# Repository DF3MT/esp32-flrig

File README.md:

<h1 align="center">ESP32 CAT Remote Panel</h1>

<p align="center"><sub><strong><a href="https://en.wikipedia.org/wiki/Computer_Aided_Transceiver">CAT</a></strong> = <a href="https://en.wikipedia.org/wiki/Computer_Aided_Transceiver">Computer Aided Transceiver</a> (not Caterpillar)</sub></p>

<p align="center">
  <a href="#deutsch">🇩🇪 Deutsch</a> ·
  <a href="#english">🇬🇧 English</a>
</p>

<p align="center">
  <strong>DE:</strong> Funkfernbedienung mit Touch-Display, <a href="https://en.wikipedia.org/wiki/Computer_Aided_Transceiver">CAT</a>, <a href="https://de.wikipedia.org/wiki/WLAN">WiFi</a>-Audio, <a href="https://de.wikipedia.org/wiki/FT8_(Amateurfunk)">FT8</a> · bis zu <strong>3× Funk + <a href="https://de.wikipedia.org/wiki/Rotor_(Antenne)">Rotor</a></strong><br>
  <strong>EN:</strong> <a href="https://en.wikipedia.org/wiki/Amateur_radio">Ham radio</a> remote panel with touch UI, <a href="https://en.wikipedia.org/wiki/Computer_Aided_Transceiver">CAT</a>, <a href="https://en.wikipedia.org/wiki/Wi-Fi">WiFi</a> audio, <a href="https://en.wikipedia.org/wiki/FT8_(digital_mode)">FT8</a> · up to <strong>3× radios + <a href="https://en.wikipedia.org/wiki/Antenna_rotator">rotor</a></strong>
</p>

<p align="center">
  <a href="https://de.wikipedia.org/wiki/Icom">ICOM</a> <a href="https://de.wikipedia.org/wiki/CI-V">CI-V</a> · <a href="https://de.wikipedia.org/wiki/Yaesu">Yaesu</a> <a href="https://en.wikipedia.org/wiki/Computer_Aided_Transceiver">CAT</a> · <a href="https://www.xiegu.com/">Xiegu</a> · <a href="https://github.com/w1hkj/flrig">flrig</a> · <a href="https://physics.princeton.edu/pulsar/k1jt/wsjtx.html">WSJT-X</a> · <a href="https://en.wikipedia.org/wiki/Hamlib">Hamlib</a> <a href="https://hamlib.sourceforge.net/html/rigctld.1.html">rigctld</a> · <a href="https://hamlib.sourceforge.net/html/rotctld.1.html">rotctld</a>
</p>

<p align="center">
  <a href="#deutsch">📖 DE</a> ·
  <a href="#english">📖 EN</a> ·
  <a href="docs/GUIDE_DE.md">Leitfaden (DE)</a> ·
  <a href="hardware/esp32-flrig-shield/README.md">🛠️ PCB</a> ·
  <a href="docs/RADIOS.md">📻 Radios</a> ·
  <a href="docs/ISOLATION.md">🔌 Isolation</a> ·
  <a href="docs/MULTI_RADIO_DE.md">📡 3× DE</a> ·
  <a href="docs/MULTI_RADIO_EN.md">📡 3× EN</a> ·
  <a href="docs/GLOSSARY.md">📚 Glossar</a> ·
  <a href="flasher/index.html">⚡ Flasher</a>
</p>

---

## Deutsch

### Was ist das?

Ein **[ESP32](https://de.wikipedia.org/wiki/ESP32)-Panel** (z. B. [Cheap Yellow Display](https://github.com/witnessmenow/ESP32-Cheap-Yellow-Display)) oder **[ESP32-S3](https://www.espressif.com/en/products/socs/esp32-s3) + Interface-Shield** steuert bis zu **drei [Funkgeräten](https://de.wikipedia.org/wiki/Transceiver) gleichzeitig** über **[WiFi](https://de.wikipedia.org/wiki/WLAN)**:

| Kanal | Anbindung | [CAT](https://en.wikipedia.org/wiki/Computer_Aided_Transceiver) → PC | Audio → PC (eigenes [UDP](https://de.wikipedia.org/wiki/User_Datagram_Protocol)-Paar) |
|-------|-----------|----------|------------------------------|
| **A** | [RJ45](https://de.wikipedia.org/wiki/RJ-45) / [I2S](https://de.wikipedia.org/wiki/I%C2%B2S) | `:4532` | `4533` / `4534` |
| **B** | [USB-A](https://de.wikipedia.org/wiki/USB) J5 | `:4536` | `4538` / `4539` |
| **C** | [USB](https://de.wikipedia.org/wiki/Universal_Serial_Bus)-A J6 | `:4540` | `4541` / `4542` |
| **[Rotor](https://de.wikipedia.org/wiki/Rotor_(Antenne))** | [GPIO](https://de.wikipedia.org/wiki/General_Purpose_Input/Output) | `:4535` | — |

Ideal für **[FT8](https://de.wikipedia.org/wiki/FT8_(Amateurfunk))/[WSJT-X](https://physics.princeton.edu/pulsar/k1jt/wsjtx.html)** am PC ohne [USB-Kabel](https://de.wikipedia.org/wiki/Universal_Serial_Bus) zum Funk. Shield **Rev C** trennt die **Masse jedes Funkgeräts [galvanisch](https://de.wikipedia.org/wiki/Galvanische_Trennung)** ([Isolation](docs/ISOLATION.md)).

**3 [Funkgeräte](https://de.wikipedia.org/wiki/Transceiver)** = am PC **3 parallele, unabhängige** Ketten (je ein [rigctld](https://hamlib.sourceforge.net/html/rigctld.1.html)-[TCP](https://de.wikipedia.org/wiki/Transmission_Control_Protocol)-Port + ein Audio-[UDP](https://de.wikipedia.org/wiki/User_Datagram_Protocol)-Paar + eigenes PC-Audiogerät, z. B. [VB-Cable](https://vb-audio.com/Cable/) A/B/C). Der ESP mischt die Streams **nicht**.

**[CAT](https://en.wikipedia.org/wiki/Computer_Aided_Transceiver)** = **[Computer Aided Transceiver](https://en.wikipedia.org/wiki/Computer_Aided_Transceiver)** (Steuerprotokoll, z. B. [CI-V](https://de.wikipedia.org/wiki/CI-V) / [Yaesu CAT](https://en.wikipedia.org/wiki/Computer_Aided_Transceiver)).

| PC-Instanz | [rigctld](https://hamlib.sourceforge.net/html/rigctld.1.html) ([CAT](https://en.wikipedia.org/wiki/Computer_Aided_Transceiver)) | Audio RX / TX ([UDP](https://de.wikipedia.org/wiki/User_Datagram_Protocol)) | Web |
|------------|---------------|---------------------|-----|
| Funk A | **4532** | **4533** / **4534** | `/audio` |
| Funk B | **4536** | **4538** / **4539** | `/audio_b` |
| Funk C | **4540** | **4541** / **4542** | `/audio_c` |
| [Rotor](https://de.wikipedia.org/wiki/Rotor_(Antenne)) | **4535** ([rotctld](https://hamlib.sourceforge.net/html/rotctld.1.html)) | — | — |

Details: [MULTI_RADIO_DE.md](docs/MULTI_RADIO_DE.md) · Beispiel-Konfig: [ft8_config.example-3radio.json](scripts/ft8_config.example-3radio.json)

### Unterstützte [Funkgeräte](https://de.wikipedia.org/wiki/Transceiver)

| Hersteller | Modelle |
|------------|---------|
| **[Xiegu](https://www.xiegu.com/)** | G90, [X6100](https://www.xiegu.com/), [X6200](https://www.xiegu.com/) |
| **[Yaesu](https://de.wikipedia.org/wiki/Yaesu)** | FT-991A, FT-910, FT-DX10, FT-DX101D/MP, FT-891, FT-897, FT-857 |
| Referenz | [ICOM](https://de.wikipedia.org/wiki/Icom) IC-7300 |

Profil in der Web-UI → Baudrate & Protokoll automatisch: [RADIOS.md](docs/RADIOS.md)

### Schnellstart

**Firmware (1× Funk, [CYD](https://github.com/witnessmenow/ESP32-Cheap-Yellow-Display)):**

```bash
pio run -e esp32-cyd -t upload
pio run -e esp32-cyd -t uploadfs
```

**Firmware (3× Funk + [Rotor](https://de.wikipedia.org/wiki/Rotor_(Antenne)), Shield Rev C + [ESP32-S3](https://www.espressif.com/en/products/socs/esp32-s3)):**

```bash
pio run -e esp32-flrig-shield -t upload
pio run -e esp32-flrig-shield -t uploadfs
```

Oder **[Web-Flasher](flasher/index.html)** im Browser.

| Modus | [SSID](https://de.wikipedia.org/wiki/Service_Set_Identifier) / IP | Konfiguration |
|-------|-----------|---------------|
| AP (Werk) | `ESP32-CAT-Panel` / `192.168.4.1` | http://192.168.4.1/ |
| [WLAN](https://de.wikipedia.org/wiki/WLAN) | [DHCP](https://de.wikipedia.org/wiki/Dynamic_Host_Configuration_Protocol) | Funkprofil wählen |

**[CAT](https://en.wikipedia.org/wiki/Computer_Aided_Transceiver) testen ([Computer Aided Transceiver](https://en.wikipedia.org/wiki/Computer_Aided_Transceiver)):**

```bash
rigctl -m 2 -r 192.168.4.1:4532 f    # Funk A
rigctl -m 2 -r 192.168.4.1:4536 f    # Funk B
rigctl -m 2 -r 192.168.4.1:4540 f    # Funk C
rotctl -m 2 -r 192.168.4.1:4535 p    # Rotor
```

### [Rotor](https://de.wikipedia.org/wiki/Rotor_(Antenne)) ([Hamlib](https://en.wikipedia.org/wiki/Hamlib) [rotctld](https://hamlib.sourceforge.net/html/rotctld.1.html))

Zwei **Taster** (Azimut) und zwei **[Open-Collector](https://de.wikipedia.org/wiki/Offener_Kollektor)-Ausgänge** für Relais ([NPN](https://de.wikipedia.org/wiki/Bipolartransistor) + [Freilaufdiode](https://de.wikipedia.org/wiki/Freilaufdiode) extern).

| Richtung (`M`) | Wert | OC-[GPIO](https://de.wikipedia.org/wiki/General_Purpose_Input/Output) ([CYD](https://github.com/witnessmenow/ESP32-Cheap-Yellow-Display)) |
|----------------|------|---------------|
| Links (CCW) | 8 | **18** |
| Rechts (CW) | 16 | **19** |
| Taster CCW / CW | — | **27** / **5** |

`OUTPUT_OPEN_DRAIN`: **LOW** = Relais ein. Port **4535** (nicht 4533 — Audio-[UDP](https://de.wikipedia.org/wiki/User_Datagram_Protocol)).

### Interface-Shield (Dokumentation)

| Dokument | Inhalt |
|----------|--------|
| [Shield README](hardware/esp32-flrig-shield/README.md#deutsch) | Übersicht (DE/EN) |
| [Schaltplan](hardware/esp32-flrig-shield/docs/SCHEMATIC.md) | Logik, Isolation |
| [Kabel](hardware/esp32-flrig-shield/docs/CABLE_ASSEMBLY.md) | RJ45 / Funk |
| [RJ45-Pinout](hardware/esp32-flrig-shield/docs/RJ45_PINOUT.md) | Steckerbelegung |

### [FT8](https://de.wikipedia.org/wiki/FT8_(Amateurfunk)) / [WSJT-X](https://physics.princeton.edu/pulsar/k1jt/wsjtx.html)

```bash
pip install -r scripts/requirements-ft8.txt
cp scripts/ft8_config.example.json ~/.config/esp32-flrig/ft8.json
python3 scripts/ft8_setup.py --config ~/.config/esp32-flrig/ft8.json --test-cat --start
```

| OS | Skript |
|----|--------|
| [Linux](https://de.wikipedia.org/wiki/Linux) | `./scripts/ft8_setup.sh 192.168.4.1 --pa --start` |
| [Windows](https://de.wikipedia.org/wiki/Microsoft_Windows) | `.\scripts\ft8_windows_setup.ps1 -EspHost 192.168.4.1 -InstallVbCable -StartBridge` |

### Hardware ([CYD](https://github.com/witnessmenow/ESP32-Cheap-Yellow-Display), Kanal A)

| Signal | [GPIO](https://de.wikipedia.org/wiki/General_Purpose_Input/Output) |
|--------|------|
| [CAT](https://en.wikipedia.org/wiki/Computer_Aided_Transceiver) RX / TX | 16 / 17 |
| [I2S](https://de.wikipedia.org/wiki/I%C2%B2S) BCLK / LRCK | 26 / 25 |
| [I2S](https://de.wikipedia.org/wiki/I%C2%B2S) DOUT / DIN | 22 / 4 |
| [Potis](https://de.wikipedia.org/wiki/Potentiometer) 1–5 | 32, 35, 34, 39, 36 |
| [Rotor](https://de.wikipedia.org/wiki/Rotor_(Antenne)) Taster / OC | 27, 5 / 18, 19 |

### Weitere Dokumentation

| Thema | Link |
|-------|------|
| Ausführlicher Leitfaden | [GUIDE_DE.md](docs/GUIDE_DE.md) (Deutsch) |
| [Hamlib](https://en.wikipedia.org/wiki/Hamlib) [rigctld](https://hamlib.sourceforge.net/html/rigctld.1.html) / [rotctld](https://hamlib.sourceforge.net/html/rotctld.1.html) | [rigctld](https://hamlib.sourceforge.net/html/rigctld.1.html) · [rotctld](https://hamlib.sourceforge.net/html/rotctld.1.html) |
| Audio-Monitor | http://\<ESP-IP\>/audio |

---

## English

### What is this?

An **[ESP32](https://en.wikipedia.org/wiki/ESP32) panel** (e.g. [Cheap Yellow Display](https://github.com/witnessmenow/ESP32-Cheap-Yellow-Display)) or **[ESP32-S3](https://www.espressif.com/en/products/socs/esp32-s3) + interface shield** controls up to **three [transceivers](https://en.wikipedia.org/wiki/Transceiver) at once** over **[WiFi](https://en.wikipedia.org/wiki/Wi-Fi)**:

| Channel | Connection | [CAT](https://en.wikipedia.org/wiki/Computer_Aided_Transceiver) → PC | Audio → PC (own [UDP](https://en.wikipedia.org/wiki/User_Datagram_Protocol) pair) |
|---------|------------|----------|---------------------------|
| **A** | [RJ45](https://en.wikipedia.org/wiki/Registered_jack) / [I2S](https://en.wikipedia.org/wiki/I%C2%B2S) | `:4532` | `4533` / `4534` |
| **B** | [USB-A](https://en.wikipedia.org/wiki/USB) J5 | `:4536` | `4538` / `4539` |
| **C** | [USB](https://en.wikipedia.org/wiki/USB)-A J6 | `:4540` | `4541` / `4542` |
| **[Rotor](https://en.wikipedia.org/wiki/Antenna_rotator)** | [GPIO](https://en.wikipedia.org/wiki/General-purpose_input/output) | `:4535` | — |

Built for **[FT8](https://en.wikipedia.org/wiki/FT8_(digital_mode))/[WSJT-X](https://physics.princeton.edu/pulsar/k1jt/wsjtx.html)** on a PC without [USB cables](https://en.wikipedia.org/wiki/USB) to each radio. Shield **Rev C** uses **[galvanic isolation](https://en.wikipedia.org/wiki/Galvanic_isolation)** per radio ([ISOLATION.md](docs/ISOLATION.md)).

**3 radios** = on the PC **3 parallel, independent** chains (one [rigctld](https://hamlib.sourceforge.net/html/rigctld.1.html) [TCP](https://en.wikipedia.org/wiki/Transmission_Control_Protocol) port + one audio [UDP](https://en.wikipedia.org/wiki/User_Datagram_Protocol) pair + separate PC audio device each, e.g. [VB-Cable](https://vb-audio.com/Cable/) A/B/C). The ESP does **not** mix streams.

**[CAT](https://en.wikipedia.org/wiki/Computer_Aided_Transceiver)** = **[Computer Aided Transceiver](https://en.wikipedia.org/wiki/Computer_Aided_Transceiver)** (control protocol) — not construction equipment.

| PC instance | [rigctld](https://hamlib.sourceforge.net/html/rigctld.1.html) ([CAT](https://en.wikipedia.org/wiki/Computer_Aided_Transceiver)) | Audio RX / TX ([UDP](https://en.wikipedia.org/wiki/User_Datagram_Protocol)) | Web |
|-------------|---------------|---------------------|-----|
| Radio A | **4532** | **4533** / **4534** | `/audio` |
| Radio B | **4536** | **4538** / **4539** | `/audio_b` |
| Radio C | **4540** | **4541** / **4542** | `/audio_c` |
| [Rotor](https://en.wikipedia.org/wiki/Antenna_rotator) | **4535** ([rotctld](https://hamlib.sourceforge.net/html/rotctld.1.html)) | — | — |

Details: [MULTI_RADIO_EN.md](docs/MULTI_RADIO_EN.md) · Example config: [ft8_config.example-3radio.json](scripts/ft8_config.example-3radio.json)

### Supported radios

| Vendor | Models |
|--------|--------|
| **[Xiegu](https://www.xiegu.com/)** | G90, X6100, X6200 |
| **[Yaesu](https://en.wikipedia.org/wiki/Yaesu_(brand))** | FT-991A, FT-910, FT-DX10, FT-DX101D/MP, FT-891, FT-897, FT-857 |
| Reference | [ICOM](https://en.wikipedia.org/wiki/Icom) IC-7300 |

Select a profile in the web UI: [RADIOS.md](docs/RADIOS.md)

### Quick start

**Firmware (single radio, [CYD](https://github.com/witnessmenow/ESP32-Cheap-Yellow-Display)):**

```bash
pio run -e esp32-cyd -t upload
pio run -e esp32-cyd -t uploadfs
```

**Firmware (3 radios + [rotor](https://en.wikipedia.org/wiki/Antenna_rotator), Shield Rev C + [ESP32-S3](https://www.espressif.com/en/products/socs/esp32-s3)):**

```bash
pio run -e esp32-flrig-shield -t upload
pio run -e esp32-flrig-shield -t uploadfs
```

Or the **[Web Flasher](flasher/index.html)** in your browser.

| Mode | [SSID](https://en.wikipedia.org/wiki/Service_set_(802.11_network)) / IP | Config |
|------|-----------|--------|
| AP (default) | `ESP32-CAT-Panel` / `192.168.4.1` | http://192.168.4.1/ |
| [WiFi](https://en.wikipedia.org/wiki/Wi-Fi) STA | [DHCP](https://en.wikipedia.org/wiki/Dynamic_Host_Configuration_Protocol) | Select radio profile |

**Test [CAT](https://en.wikipedia.org/wiki/Computer_Aided_Transceiver) ([Computer Aided Transceiver](https://en.wikipedia.org/wiki/Computer_Aided_Transceiver)):**

```bash
rigctl -m 2 -r 192.168.4.1:4532 f    # Radio A
rigctl -m 2 -r 192.168.4.1:4536 f    # Radio B
rigctl -m 2 -r 192.168.4.1:4540 f    # Radio C
rotctl -m 2 -r 192.168.4.1:4535 p    # Rotor
```

### [Rotor](https://en.wikipedia.org/wiki/Antenna_rotator) ([Hamlib](https://en.wikipedia.org/wiki/Hamlib) [rotctld](https://hamlib.sourceforge.net/html/rotctld.1.html))

Two **buttons** (azimuth) and two **[open-collector](https://en.wikipedia.org/wiki/Open_collector)** outputs for relays (external [NPN](https://en.wikipedia.org/wiki/Bipolar_junction_transistor) + [flyback diode](https://en.wikipedia.org/wiki/Flyback_diode)).

| Direction (`M`) | Value | OC [GPIO](https://en.wikipedia.org/wiki/General-purpose_input/output) ([CYD](https://github.com/witnessmenow/ESP32-Cheap-Yellow-Display)) |
|-----------------|-------|---------------|
| Left (CCW) | 8 | **18** |
| Right (CW) | 16 | **19** |
| Buttons CCW / CW | — | **27** / **5** |

`OUTPUT_OPEN_DRAIN`: **LOW** = relay on. Port **4535** (not 4533 — audio [UDP](https://en.wikipedia.org/wiki/User_Datagram_Protocol)).

### Interface shield (documentation)

| Document | Content |
|----------|---------|
| [Shield README](hardware/esp32-flrig-shield/README.md#english) | Overview (DE/EN) |
| [Schematic](hardware/esp32-flrig-shield/docs/SCHEMATIC.md) | Logic, isolation |
| [Cables](hardware/esp32-flrig-shield/docs/CABLE_ASSEMBLY.md) | RJ45 / radio |
| [RJ45 pinout](hardware/esp32-flrig-shield/docs/RJ45_PINOUT.md) | Connector pins |

### [FT8](https://en.wikipedia.org/wiki/FT8_(digital_mode)) / [WSJT-X](https://physics.princeton.edu/pulsar/k1jt/wsjtx.html)

```bash
pip install -r scripts/requirements-ft8.txt
cp scripts/ft8_config.example.json ~/.config/esp32-flrig/ft8.json
python3 scripts/ft8_setup.py --config ~/.config/esp32-flrig/ft8.json --test-cat --start
```

| OS | Script |
|----|--------|
| [Linux](https://en.wikipedia.org/wiki/Linux) | `./scripts/ft8_setup.sh 192.168.4.1 --pa --start` |
| [Windows](https://en.wikipedia.org/wiki/Microsoft_Windows) | `.\scripts\ft8_windows_setup.ps1 -EspHost 192.168.4.1 -InstallVbCable -StartBridge` |

### Hardware ([CYD](https://github.com/witnessmenow/ESP32-Cheap-Yellow-Display), channel A)

| Signal | [GPIO](https://en.wikipedia.org/wiki/General-purpose_input/output) |
|--------|------|
| [CAT](https://en.wikipedia.org/wiki/Computer_Aided_Transceiver) RX / TX | 16 / 17 |
| [I2S](https://en.wikipedia.org/wiki/I%C2%B2S) BCLK / LRCK | 26 / 25 |
| [I2S](https://en.wikipedia.org/wiki/I%C2%B2S) DOUT / DIN | 22 / 4 |
| Pots 1–5 | 32, 35, 34, 39, 36 |
| [Rotor](https://en.wikipedia.org/wiki/Antenna_rotator) buttons / OC | 27, 5 / 18, 19 |

[CAT](https://en.wikipedia.org/wiki/Computer_Aided_Transceiver) on [CYD](https://github.com/witnessmenow/ESP32-Cheap-Yellow-Display): **3.3 V [TTL](https://en.wikipedia.org/wiki/Transistor%E2%80%93transistor_logic)**; on the shield **[ISO7741](https://www.ti.com/product/ISO7741)** isolates [RJ45](https://en.wikipedia.org/wiki/Registered_jack) [CAT](https://en.wikipedia.org/wiki/Computer_Aided_Transceiver) from ESP ground.

### Project layout

```
esp32-flrig/
├── docs/              Guides, radio list, isolation
├── hardware/esp32-flrig-shield/
│   ├── docs/          Schematic, cables, RJ45
│   └── assets/        Block diagram
├── scripts/           FT8 setup (Linux / Windows)
├── src/               Firmware
└── flasher/           Browser flasher
```

### Architecture

```
┌─────────────┐  rigctld :4532/4536/4540   ┌──────────────┐  isolated   ┌─────────┐
│ WSJT-X/flrig│◄──────────────────────────►│ ESP32 Panel  │◄───────────►│ 3× Radio│
└─────────────┘                            │ rotctld :4535│             └─────────┘
┌─────────────┐  rotctl                    │ WiFi audio   │
│ rotctl      │◄──────────────────────────►│ Touch + Web  │
└─────────────┘                            └──────────────┘
```

### More links

| Topic | Link |
|-------|------|
| Full guide | [GUIDE_DE.md](docs/GUIDE_DE.md) (German) |
| [Hamlib](https://en.wikipedia.org/wiki/Hamlib) [rigctld](https://hamlib.sourceforge.net/html/rigctld.1.html) / [rotctld](https://hamlib.sourceforge.net/html/rotctld.1.html) | [rigctld](https://hamlib.sourceforge.net/html/rigctld.1.html) · [rotctld](https://hamlib.sourceforge.net/html/rotctld.1.html) |
| Audio monitor | http://\<ESP-IP\>/audio |

---

<p align="center">
  <sub>License: see repository · Contributions welcome · <a href="#deutsch">🇩🇪</a> · <a href="#english">🇬🇧</a></sub>
</p>

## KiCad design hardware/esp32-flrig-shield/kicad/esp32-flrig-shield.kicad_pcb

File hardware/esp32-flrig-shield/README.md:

# ESP32-FLRIG Interface Shield

<p align="center">
  <a href="#deutsch">🇩🇪 Deutsch</a> ·
  <a href="#english">🇬🇧 English</a>
</p>

<p align="center">
  <sub><strong><a href="https://en.wikipedia.org/wiki/Computer_Aided_Transceiver">CAT</a></strong> = <a href="https://en.wikipedia.org/wiki/Computer_Aided_Transceiver">Computer Aided Transceiver</a></sub>
</p>

---

## Deutsch

### Übersicht

Dokumentation für ein **Interface-Shield** zwischen **[ESP32-S3](https://www.espressif.com/en/products/socs/esp32-s3)** ([USB-Host](https://de.wikipedia.org/wiki/USB)) bzw. optional **[CYD](https://github.com/witnessmenow/ESP32-Cheap-Yellow-Display)** (nur Funk **Kanal A**) und bis zu **drei Funkgeräten**:

| Anschluss | Funktion |
|-----------|----------|
| **J1 [RJ45](https://de.wikipedia.org/wiki/RJ-45)** | Funk **A**: +5 V, **[CAT](https://en.wikipedia.org/wiki/Computer_Aided_Transceiver)** ([UART](https://de.wikipedia.org/wiki/Asynchrone_Serielle_Schnittstelle)), **Line-Audio** |
| **J5 / J6** | **[USB-A](https://de.wikipedia.org/wiki/USB) Buchse** — Funk **B** und **C** ([CAT](https://en.wikipedia.org/wiki/Computer_Aided_Transceiver) + Audio per [USB](https://de.wikipedia.org/wiki/Universal_Serial_Bus)) |
| **U5 [USB2422](https://www.microchip.com/en-us/product/USB2422)** | 2-Port-Hub, Upstream **J3** → [ESP32-S3](https://www.espressif.com/en/products/socs/esp32-s3) OTG |
| **J7 / J3** | **[Rotor](https://de.wikipedia.org/wiki/Rotor_(Antenne))** (2× Taster, 2× [Open-Collector](https://de.wikipedia.org/wiki/Offener_Kollektor)) |
| **J2** | 2×10 für **[CYD](https://github.com/witnessmenow/ESP32-Cheap-Yellow-Display)** (Kanal A + [I2S](https://de.wikipedia.org/wiki/I%C2%B2S)) |

- **U1 [ISO7741](https://www.ti.com/product/ISO7741)** — [CAT](https://en.wikipedia.org/wiki/Computer_Aided_Transceiver) [galvanisch getrennt](https://de.wikipedia.org/wiki/Galvanische_Trennung) ([RJ45](https://de.wikipedia.org/wiki/RJ-45))  
- **U6/U7 [ADuM4160](https://www.analog.com/en/products/adum4160.html)** — [USB](https://de.wikipedia.org/wiki/Universal_Serial_Bus) [galvanisch](https://de.wikipedia.org/wiki/Galvanische_Trennung) getrennt (Funk B/C)  
- **T1/T2** — [Audio-Trafos](https://de.wikipedia.org/wiki/Transformator) (Funk A)  
- **[PCM5102](https://www.ti.com/product/PCM5102) + [INMP441](https://www.invensense.com/products/digital/inmp441/)** — [I2S](https://de.wikipedia.org/wiki/I%C2%B2S) (48 [kHz](https://de.wikipedia.org/wiki/Hertz))  

**3× Funk + 1× [Rotor](https://de.wikipedia.org/wiki/Rotor_(Antenne))** über **[WiFi](https://de.wikipedia.org/wiki/WLAN)**. **Keine gemeinsame Masse** zwischen den [Funkgeräten](https://de.wikipedia.org/wiki/Transceiver): [Isolation](../../docs/ISOLATION.md).

**Am PC:** drei getrennte [rigctld](https://hamlib.sourceforge.net/html/rigctld.1.html)-Verbindungen und drei Audio-[UDP](https://de.wikipedia.org/wiki/User_Datagram_Protocol)-Paare — siehe [MULTI_RADIO_DE.md](../../docs/MULTI_RADIO_DE.md).

### Dokumentation

| Thema | Datei |
|-------|--------|
| Logischer Schaltplan | [SCHEMATIC.md](docs/SCHEMATIC.md) |
| Kabel / RJ45 | [CABLE_ASSEMBLY.md](docs/CABLE_ASSEMBLY.md) · [RJ45_PINOUT.md](docs/RJ45_PINOUT.md) |
| Isolation | [ISOLATION.md](../../docs/ISOLATION.md) |

### Firmware

```bash
pio run -t upload -e esp32-flrig-shield
pio run -t uploadfs -e esp32-flrig-shield
```

### [Rotor](https://de.wikipedia.org/wiki/Rotor_(Antenne)) ([GPIO](https://de.wikipedia.org/wiki/General_Purpose_Input/Output))

| J7 / J3 | [GPIO](https://de.wikipedia.org/wiki/General_Purpose_Input/Output) (S3-Default) |
|---------|-------------------|
| Taster CCW | 27 |
| Taster CW | 5 |
| [Open Collector](https://de.wikipedia.org/wiki/Offener_Kollektor) CCW | 18 |
| [Open Collector](https://de.wikipedia.org/wiki/Offener_Kollektor) CW | 19 |

**[rotctld](https://hamlib.sourceforge.net/html/rotctld.1.html)** Port **4535**.

### Dateien

```
esp32-flrig-shield/
├── docs/     Schaltplan, Kabel, RJ45
└── assets/   Blockdiagramm (SVG)
```

---

## English

### Overview

Documentation for an **interface shield** between **[ESP32-S3](https://www.espressif.com/en/products/socs/esp32-s3)** ([USB host](https://en.wikipedia.org/wiki/USB)) or optionally **[CYD](https://github.com/witnessmenow/ESP32-Cheap-Yellow-Display)** (radio **channel A** only) and up to **three radios**:

| Connector | Function |
|-----------|----------|
| **J1 [RJ45](https://en.wikipedia.org/wiki/Registered_jack)** | Radio **A**: +5 V, **[CAT](https://en.wikipedia.org/wiki/Computer_Aided_Transceiver)** ([UART](https://en.wikipedia.org/wiki/Universal_asynchronous_receiver-transmitter)), line audio |
| **J5 / J6** | **[USB Type-A](https://en.wikipedia.org/wiki/USB)** — radios **B** and **C** |
| **U5 [USB2422](https://www.microchip.com/en-us/product/USB2422)** | 2-port hub, upstream **J3** → [ESP32-S3](https://www.espressif.com/en/products/socs/esp32-s3) OTG |
| **J7 / J3** | **[Rotor](https://en.wikipedia.org/wiki/Antenna_rotator)** (2× buttons, 2× [open-collector](https://en.wikipedia.org/wiki/Open_collector)) |
| **J2** | 2×10 header for **[CYD](https://github.com/witnessmenow/ESP32-Cheap-Yellow-Display)** |

See [ISOLATION.md](../../docs/ISOLATION.md) and [MULTI_RADIO_EN.md](../../docs/MULTI_RADIO_EN.md).

### Documentation

| Topic | File |
|-------|------|
| Logical schematic | [SCHEMATIC.md](docs/SCHEMATIC.md) |
| Cables / RJ45 | [CABLE_ASSEMBLY.md](docs/CABLE_ASSEMBLY.md) · [RJ45_PINOUT.md](docs/RJ45_PINOUT.md) |

### Firmware

```bash
pio run -t upload -e esp32-flrig-shield
pio run -t uploadfs -e esp32-flrig-shield
```

### [Rotor](https://en.wikipedia.org/wiki/Antenna_rotator) ([GPIO](https://en.wikipedia.org/wiki/General-purpose_input/output))

| J7 / J3 | GPIO (S3 default) |
|---------|-------------------|
| Button CCW | 27 |
| Button CW | 5 |
| [Open collector](https://en.wikipedia.org/wiki/Open_collector) CCW | 18 |
| [Open collector](https://en.wikipedia.org/wiki/Open_collector) CW | 19 |

**[rotctld](https://hamlib.sourceforge.net/html/rotctld.1.html)** port **4535**.

---

<p align="center">
  <sub><a href="#deutsch">🇩🇪</a> · <a href="#english">🇬🇧</a> · <a href="../../README.md">Project README</a></sub>
</p>

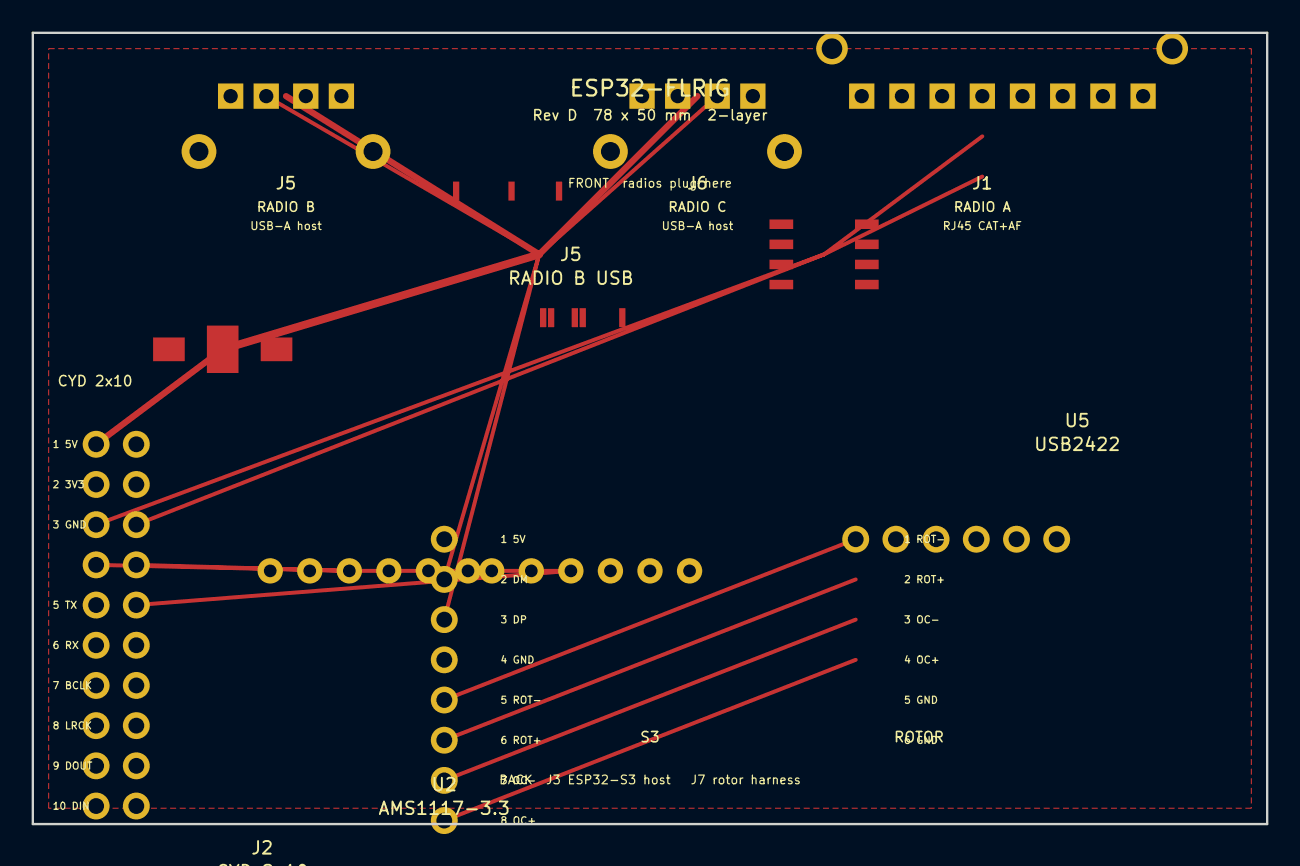
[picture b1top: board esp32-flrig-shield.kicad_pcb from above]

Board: 2 copper layers, 78.0 x 50.0 mm, 11 parts (0 on the bottom side), 25 nets.

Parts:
J1: RADIO A; RJ45_RJHSE5080
J2: CYD 2x10; PinHeader_2x10_P2.54mm_Vertical
J3: ESP32-S3 HOST; PinHeader_1x08_P2.54mm_Vertical
J5: RADIO B USB; USB_A_Host_Receptacle_Vertical
J6: RADIO C USB; USB_A_Host_Receptacle_Vertical
J7: ROTOR; PinHeader_1x06_P2.54mm_Vertical
U1: ISO7741; SOIC-8_3.9x4.9mm_P1.27mm
U2: AMS1117-3.3; SOT-223-3_TabPin2
U3: PCM5102; PCM5102_Module_6pin
U4: INMP441; INMP441_Module_6pin
U5: USB2422; USB2422_SSOP

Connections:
+3V3: J2.2, U1.1, U2.3, U3.VCC, U4.VDD
+5V_BUS: J1.1, J2.1, J3.1, J5.VBUS, J6.VBUS, U1.8, U2.2, U5.8
AF_OUT: J1.6, U3.VOUT
CAT_ESP_RX: J2.6, U1.3
CAT_ESP_TX: J2.5, U1.2
CAT_RX_RADIO: J1.4, U1.6
CAT_TX_RADIO: J1.3, U1.7
GND_ESP: J2.3, J2.4, J2.11, J2.12, J2.13, J2.14, J2.15, J2.16, J2.17, J2.18, J2.19, J2.20, J3.4, J7.5, J7.6, U1.4, U2.1, U3.GND, U4.GND, U4.LR, U5.1
GND_RADIO_A: J1.2, J1.7, J1.SH, U1.5
GND_USB_B: J5.GND, J5.SH
GND_USB_C: J6.GND, J6.SH
I2S_BCLK: J2.7, U3.BCK, U4.SCK
I2S_DIN: J2.10, U4.SD
I2S_DOUT: J2.9, U3.DIN
I2S_LRCK: J2.8, U3.LRCK, U4.WS
ROTOR_BTN_CCW: J3.5, J7.1
ROTOR_BTN_CW: J3.6, J7.2
ROTOR_OC_CCW: J3.7, J7.3
ROTOR_OC_CW: J3.8, J7.4
USB_DM_D1: J5.D-, U5.21
USB_DM_D2: J6.D-, U5.25
USB_DP_D1: J5.D+, U5.20
USB_DP_D2: J6.D+, U5.24
USB_OTG_DM: J3.2, U5.15
USB_OTG_DP: J3.3, U5.14

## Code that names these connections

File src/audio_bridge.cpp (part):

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
bool AudioBridge::initI2s() {
    const uint32_t rate = _ch->audioSampleRate;
    int bclk = I2S_BCLK_PIN, lrck = I2S_LRCK_PIN, dout = I2S_DOUT_PIN, din = I2S_DIN_PIN;

    _i2sPort = (_channelIndex == 0) ? (int)I2S_NUM_0 : (int)I2S_NUM_1;
    if (_channelIndex > 0) {
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
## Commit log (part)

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2026-06-03 firstCommit
2026-06-03 Rotor Implementation, audio bridge and more tranceivers
2026-06-03 some bugfixes
2026-06-03 preview images created
2026-06-03 some bugfixes with images and pcb, aswell as linking to the sources of knowledge
2026-06-03 minor correction
2026-06-03 remove pcb
